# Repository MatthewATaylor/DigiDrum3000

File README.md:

# DigiDrum3000

A real-time FPGA drum sampler, audio effects processor, and audio interface. Visit the [project webpage](https://matthewalantaylor.net/fpga-drums.html) for more information, including a selection of audio demos.

## Branches
- **nexys_a7:** Most recent revision of the project, compatibile with the Nexys A7 FPGA development board (AMD Artix-7). Includes Ethernet audio interface functionality and expression pedal control.
- **urbana:** Original project designed for the Real Digital Urbana FPGA development board (AMD Spartan-7). Developed as the final project for MIT's 6.2050 (Digital Systems Laboratory I). Includes audio visualization functionality.

## Feature Overview (nexys\_a7)
- Drum set audio samples (16-bit, 48 ksps) loaded over UART and stored in DRAM
- MIDI interface for audio sample triggering via an electronic drum set
- Audio effects
  - Pitch shift (resampling)
  - Delay
  - Stereo reverb (Freeverb)
  - Resonant low-pass filter (4-pole transistor ladder filter model)
  - Distortion (tanh)
  - Bit crush
- PCB with patch bay and knobs for controlling effects parameters
- PCB with line-level audio output (TAD5242 DAC) and expression pedal inputs
- UART interface for effects parameter automation in a digital audio workstation
- Audio recording over Ethernet with up to 12 channels of 16-bit samples at 48 ksps.
- 1.5 ms maximum audio latency (from received MIDI message to audio output)
- Extensive testing with cocotb

## Operation
1. Build
```
vivado -mode batch -source build.tcl -tclargs outputDir=<OUTPUT DIRECTORY>
```
2. Program
```
openFPGALoader -b <BOARD_NAME> <OUTPUT DIRECTORY>/final.bit
```
3. Load audio samples
```
python scripts/send_wav.py
```
4. (Optional) Run UART effects parameter controller. Create a new virtual MIDI port if one does not already exist.
```
python scripts/uart_param_controller.py
```
5. (Optional) Run Ethernet audio receiver (requires Linux with PipeWire).
```
cd ethernet_audio_interface
make
./build/ethernet_audio_interface
```

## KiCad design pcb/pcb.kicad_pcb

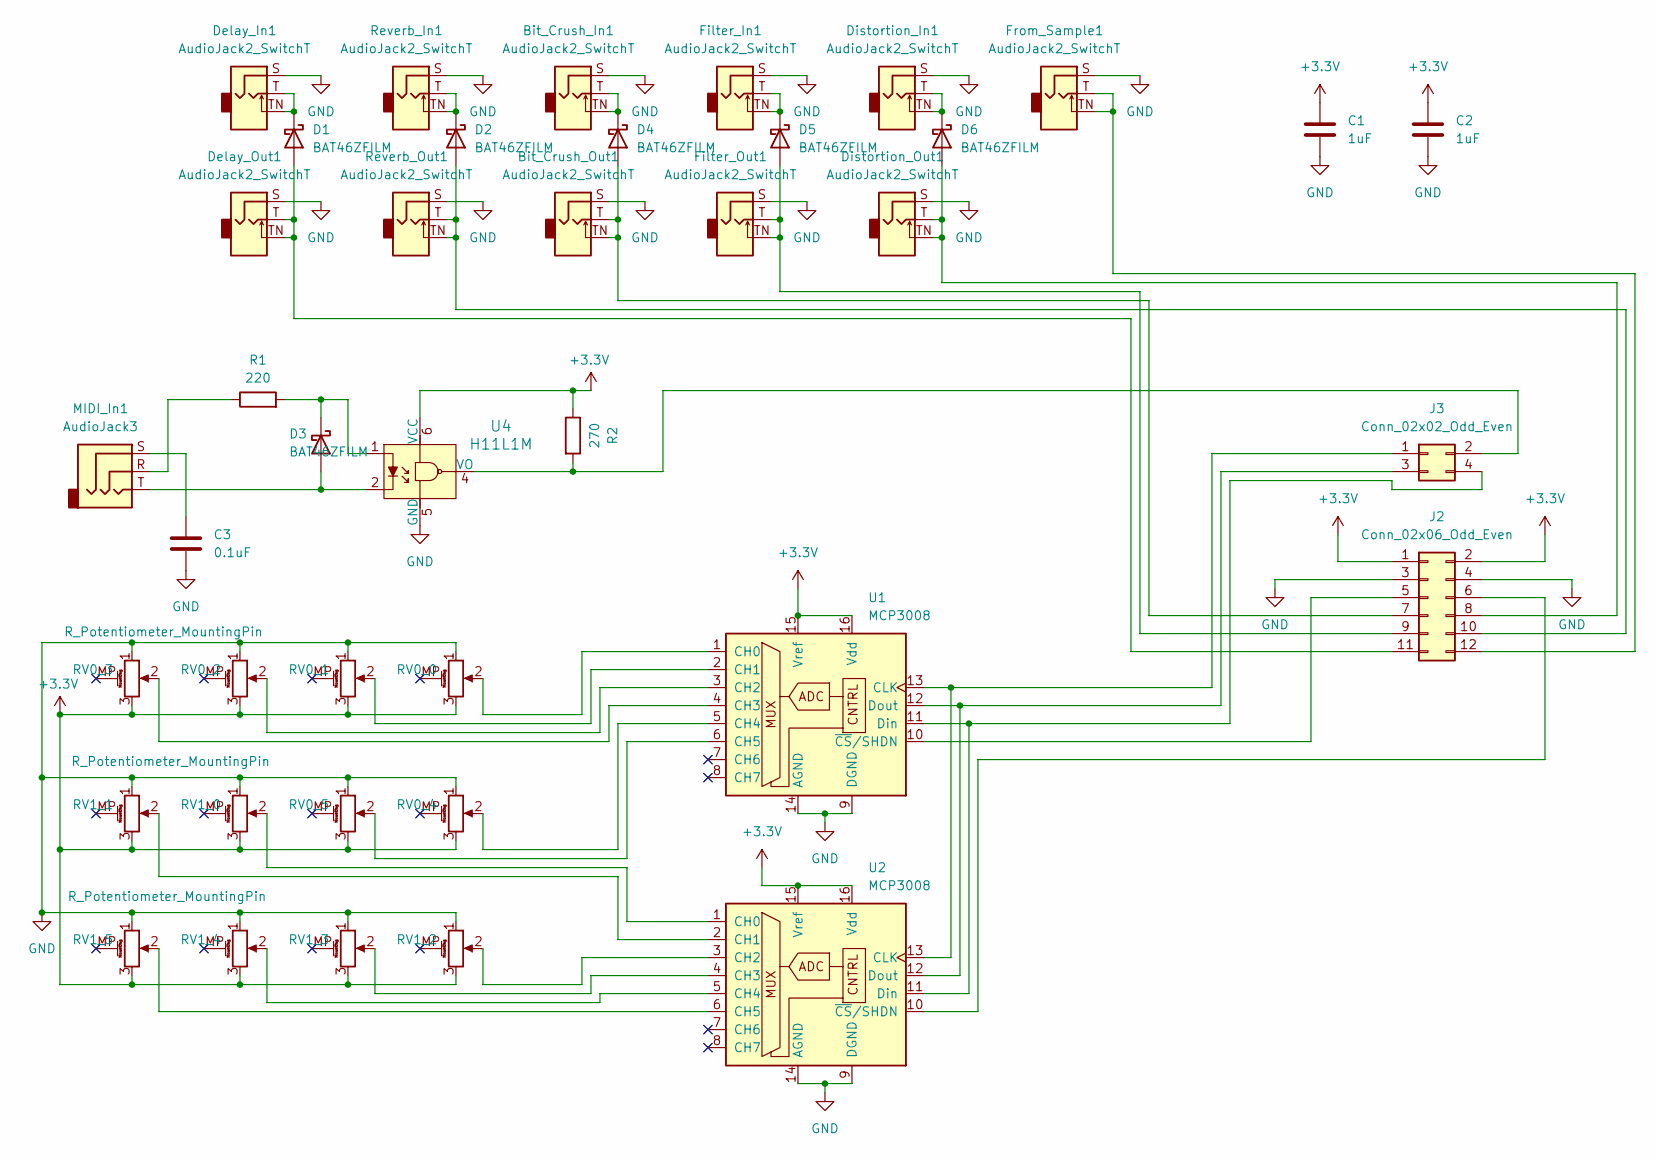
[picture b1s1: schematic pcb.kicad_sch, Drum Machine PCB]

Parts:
Bit_Crush_In1: AudioJack2_SwitchT; Jack_3.5mm_QingPu_WQP-PJ398SM_Vertical_CircularHoles
Bit_Crush_Out1: AudioJack2_SwitchT; Jack_3.5mm_QingPu_WQP-PJ398SM_Vertical_CircularHoles
C1, C2: 1uF; 0805
C3: 0.1uF; 0805
D1, D2, D3, D4, D5, D6: BAT46ZFILM; D_SOD-123
Delay_In1: AudioJack2_SwitchT; Jack_3.5mm_QingPu_WQP-PJ398SM_Vertical_CircularHoles
Delay_Out1: AudioJack2_SwitchT; Jack_3.5mm_QingPu_WQP-PJ398SM_Vertical_CircularHoles
Distortion_In1: AudioJack2_SwitchT; Jack_3.5mm_QingPu_WQP-PJ398SM_Vertical_CircularHoles
Distortion_Out1: AudioJack2_SwitchT; Jack_3.5mm_QingPu_WQP-PJ398SM_Vertical_CircularHoles
Filter_In1: AudioJack2_SwitchT; Jack_3.5mm_QingPu_WQP-PJ398SM_Vertical_CircularHoles
Filter_Out1: AudioJack2_SwitchT; Jack_3.5mm_QingPu_WQP-PJ398SM_Vertical_CircularHoles
From_Sample1: AudioJack2_SwitchT; Jack_3.5mm_QingPu_WQP-PJ398SM_Vertical_CircularHoles
J2: Conn_02x06_Odd_Even; PinHeader_2x06_P2.54mm_Horizontal
J3: Conn_02x02_Odd_Even; PinHeader_2x02_P2.54mm_Horizontal
MIDI_In1: AudioJack3; Jack_3.5mm_QingPu_WQP-PJ366ST_Vertical_CircularHoles
R1: 220; 0805
R2: 270; 0805
RV0_0, RV0_1, RV0_2, RV0_3, RV0_4, RV0_5, RV1_0, RV1_1, RV1_2, RV1_3, RV1_4, RV1_5: R_Potentiometer_MountingPin; Potentiometer_Alpha_RD901F-40-00D_Single_Vertical_MP
Reverb_In1: AudioJack2_SwitchT; Jack_3.5mm_QingPu_WQP-PJ398SM_Vertical_CircularHoles
Reverb_Out1: AudioJack2_SwitchT; Jack_3.5mm_QingPu_WQP-PJ398SM_Vertical_CircularHoles
U1, U2: MCP3008; SOIC-16_W3.90mm
U4: H11L1M; DIP-6_W7.62mm; MPN H11L1M; Digi-Key_PN H11L1-MQT-ND

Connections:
+3.3V: C1.1, C2.1, J2.1, J2.2, R2.1, RV0_0.3, RV0_1.3, RV0_2.3, RV0_3.3, RV0_4.3, RV0_5.3, RV1_0.3, RV1_1.3, RV1_2.3, RV1_3.3, RV1_4.3, RV1_5.3, U1.15 (Vref), U1.16 (Vdd), U2.15 (Vref), U2.16 (Vdd), U4.6 (VCC)
GND: Bit_Crush_In1.S, Bit_Crush_Out1.S, C1.2, C2.2, C3.2, Delay_In1.S, Delay_Out1.S, Distortion_In1.S, Distortion_Out1.S, Filter_In1.S, Filter_Out1.S, From_Sample1.S, J2.3, J2.4, RV0_0.1, RV0_1.1, RV0_2.1, RV0_3.1, RV0_4.1, RV0_5.1, RV1_0.1, RV1_1.1, RV1_2.1, RV1_3.1, RV1_4.1, RV1_5.1, Reverb_In1.S, Reverb_Out1.S, U1.9 (DGND), U1.14 (AGND), U2.9 (DGND), U2.14 (AGND), U4.5 (GND)
unnamed: C3.1, MIDI_In1.S
unnamed: D1.2 (A), Delay_Out1.T, Delay_Out1.TN, J2.11
unnamed: D1.1 (K), Delay_In1.T, Delay_In1.TN
unnamed: D2.2 (A), J2.10, Reverb_Out1.T, Reverb_Out1.TN
unnamed: D2.1 (K), Reverb_In1.T, Reverb_In1.TN
unnamed: D3.2 (A), MIDI_In1.T, U4.2
unnamed: D3.1 (K), R1.2, U4.1
unnamed: Bit_Crush_Out1.T, Bit_Crush_Out1.TN, D4.2 (A), J2.7
unnamed: Bit_Crush_In1.T, Bit_Crush_In1.TN, D4.1 (K)
unnamed: D5.2 (A), Filter_Out1.T, Filter_Out1.TN, J2.9
unnamed: D5.1 (K), Filter_In1.T, Filter_In1.TN
unnamed: D6.2 (A), Distortion_Out1.T, Distortion_Out1.TN, J2.8
unnamed: D6.1 (K), Distortion_In1.T, Distortion_In1.TN
unnamed: J2.5, U1.10 (~CS/SHDN)
unnamed: J2.6, U2.10 (~CS/SHDN)
unnamed: From_Sample1.T, From_Sample1.TN, J2.12
unnamed: J3.1, U1.13 (CLK), U2.13 (CLK)
unnamed: J3.2, R2.2, U4.4 (VO)
unnamed: J3.3, U1.12 (Dout), U2.12 (Dout)
unnamed: J3.4, U1.11 (Din), U2.11 (Din)
unnamed: MIDI_In1.R, R1.1
unnamed: RV0_0.2, U1.1 (CH0)
unnamed: RV0_1.2, U1.2 (CH1)
unnamed: RV0_2.2, U1.3 (CH2)
unnamed: RV0_3.2, U1.4 (CH3)
unnamed: RV0_4.2, U1.5 (CH4)
unnamed: RV0_5.2, U1.6 (CH5)
unnamed: RV1_0.2, U2.1 (CH0)
unnamed: RV1_1.2, U2.2 (CH1)
unnamed: RV1_2.2, U2.3 (CH2)
unnamed: RV1_3.2, U2.4 (CH3)
unnamed: RV1_4.2, U2.5 (CH4)
unnamed: RV1_5.2, U2.6 (CH5)

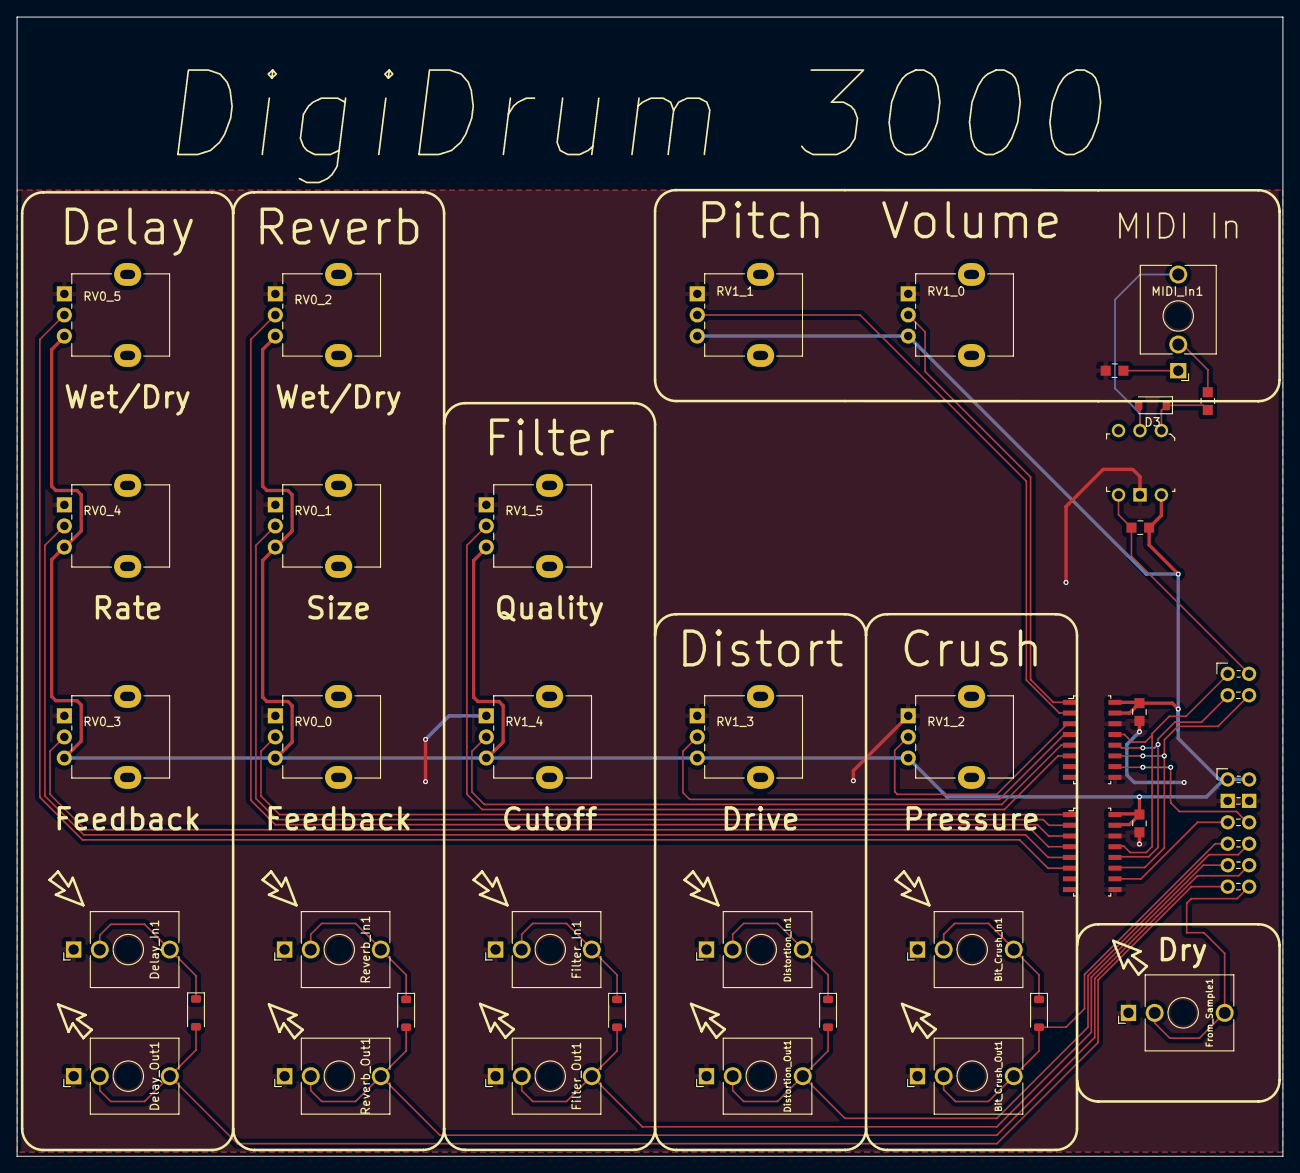
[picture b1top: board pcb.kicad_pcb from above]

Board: 2 copper layers, 150.0 x 135.0 mm, 40 parts (0 on the bottom side), 35 nets.

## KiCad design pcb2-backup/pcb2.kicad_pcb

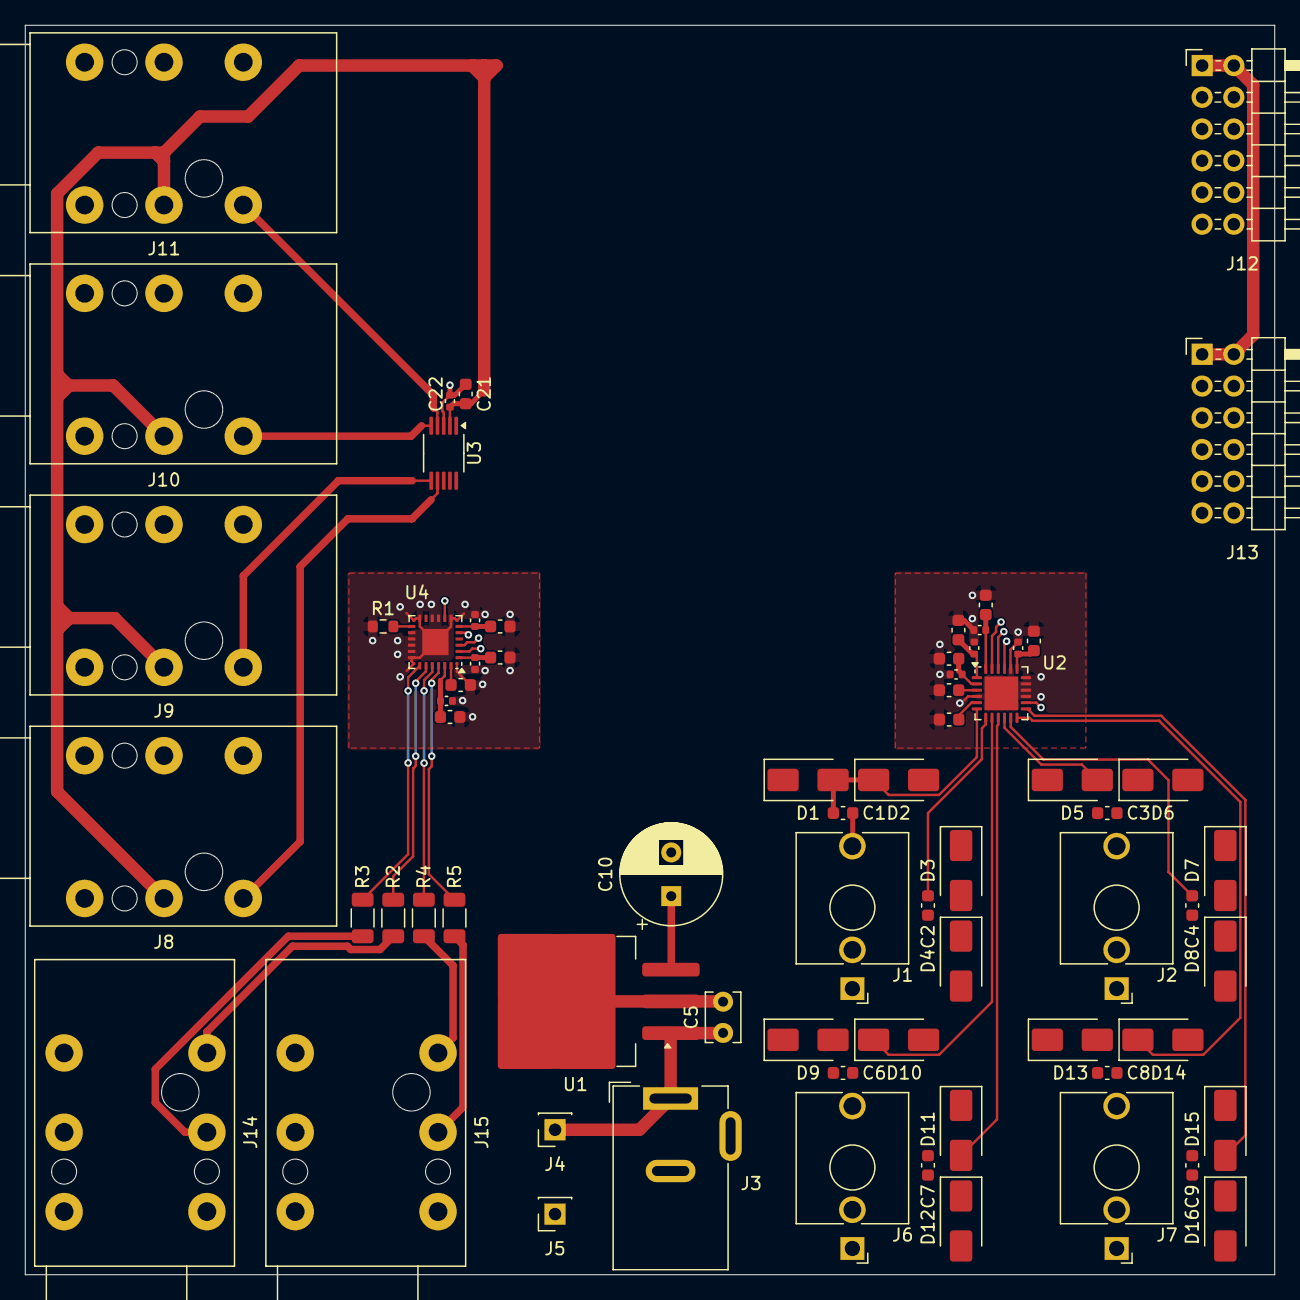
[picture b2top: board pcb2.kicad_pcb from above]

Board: 2 copper layers, 100.0 x 100.0 mm, 69 parts (0 on the bottom side), 50 nets.

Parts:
C1, C2, C3, C4, C6, C7, C8, C9, C14, C17, C19, C23, C26, C28: 10u; C_0603_1608Metric
C5: 4.7u; C_Disc_D3.8mm_W2.6mm_P2.50mm
C10: 100u; CP_Radial_D8.0mm_P3.50mm
C11, C13, C16, C21, C25: 1u; C_0603_1608Metric
C12, C15, C18, C20, C22, C24, C27, C29: 0.1u; C_0402_1005Metric
D1, D2, D3, D4, D5, D6, D7, D8, D9, D10, D11, D12, D13, D14, D15, D16: SS14; D_SMA
J1: WQP419GR_audio_in_1; Jack_3.5mm_QingPu_WQP-PJ366ST_Vertical_CircularHoles
J2: WQP419GR_audio_in_3; Jack_3.5mm_QingPu_WQP-PJ366ST_Vertical_CircularHoles
J3: Barrel_+5V_in; BarrelJack_Wuerth_6941xx301002
J4: Conn_+5V_to_FPGA; PinSocket_1x01_P2.54mm_Vertical
J5: Conn_GND_to_FPGA; PinSocket_1x01_P2.54mm_Vertical
J6: WQP419GR_audio_in_2; Jack_3.5mm_QingPu_WQP-PJ366ST_Vertical_CircularHoles
J7: WQP419GR_audio_in_4; Jack_3.5mm_QingPu_WQP-PJ366ST_Vertical_CircularHoles
J8: ACJS-HHOP_pedal_1; Jack_6.35mm_Neutrik_NRJ6HH_Horizontal
J9: ACJS-HHOP_pedal_2; Jack_6.35mm_Neutrik_NRJ6HH_Horizontal
J10: ACJS-HHOP_pedal_3; Jack_6.35mm_Neutrik_NRJ6HH_Horizontal
J11: ACJS-HHOP_pedal_4; Jack_6.35mm_Neutrik_NRJ6HH_Horizontal
J12: PMOD_JD; PinHeader_2x06_P2.54mm_Horizontal
J13: PMOD_JC; PinHeader_2x06_P2.54mm_Horizontal
J14: ACJS-HHOP_audio_out_L; Jack_6.35mm_Neutrik_NRJ6HH_Horizontal
J15: ACJS-HHOP_audio_out_R; Jack_6.35mm_Neutrik_NRJ6HH_Horizontal
R1: 4.7k; R_0603_1608Metric
R2, R3, R4, R5: 1k; R_1206_3216Metric
U1: LM3940; TO-263-3_TabPin2
U2: PCM1840; Texas_RTW_WQFN-24-1EP_4x4mm_P0.5mm_EP2.7x2.7mm
U3: ADC104S021; VSSOP-10_3x3mm_P0.5mm
U4: TAD5242; Texas_RGE0024C_VQFN-24-1EP_4x4mm_P0.5mm_EP2.1x2.1mm_CornerP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

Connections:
+3.3V: C17.1, C18.1, C21.1, C22.1, C26.1, C27.1, J8.R, J9.R, J10.R, J11.R, J12.1, J12.2, J13.1, J13.2, U2.19 (IOVDD), U3.2 (VA), U4.6 (IOVDD), U4.8 (MD2)
+3.3VA: C10.1, C11.2, C12.2, C23.2, C24.2, D1.1 (K), D3.1 (K), D5.1 (K), D7.1 (K), D9.1 (K), D11.1 (K), D13.1 (K), D15.1 (K), U1.3 (OUT), U2.1 (AVDD), U4.23 (AVDD)
+5V: C5.1, J3.1, J4.1 (Pin_1_1), U1.1 (IN)
/ADC_AUDIO_CLK: J13.8, U2.22 (BCLK)
/ADC_AUDIO_DOUT: J13.10, U2.21 (SDOUT)
/ADC_AUDIO_FSYNC: J13.6, U2.23 (FSYNC)
/ADC_AUDIO_SHDNZ: J13.12, U2.14 (SHDNZ)
/ADC_IN1N: C2.2, D3.2 (A), D4.1 (K), U2.7 (IN1N)
/ADC_IN1P: C1.2, D1.2 (A), D2.1 (K), U2.6 (IN1P)
/ADC_IN2N: C7.2, D11.2 (A), D12.1 (K), U2.9 (IN2N)
/ADC_IN2P: C6.2, D9.2 (A), D10.1 (K), U2.8 (IN2P)
/ADC_IN3N: C4.2, D7.2 (A), D8.1 (K), U2.11 (IN3N)
/ADC_IN3P: C3.2, D5.2 (A), D6.1 (K), U2.10 (IN3P)
/ADC_IN4N: C9.2, D15.2 (A), D16.1 (K), U2.13 (IN4N)
/ADC_IN4P: C8.2, D13.2 (A), D14.1 (K), U2.12 (IN4P)
/ADC_PEDAL_CLK: J13.5, U3.10 (SCLK)
/ADC_PEDAL_CS: J13.11, U3.1 (~CS)
/ADC_PEDAL_DIN: J13.9, U3.8 (DIN)
/ADC_PEDAL_DOUT: J13.7, U3.9 (DOUT)
/DAC_CLK: J12.9, U4.2 (BCLK)
/DAC_DIN: J12.11, U4.5 (DIN)
/DAC_FSYNC: J12.7, U4.3 (FSYNC)
/DAC_OUT1N: R3.2, U4.19 (OUT1N)
/DAC_OUT1P: R2.1, U4.20 (OUT1P)
/DAC_OUT2N: R5.2, U4.22 (OUT2N)
/DAC_OUT2P: R4.1, U4.21 (OUT2P)
GND: C5.2, C10.2, C11.1, C12.1, C13.1, C14.1, C15.1, C16.2, C17.2, C18.2, C19.2, C20.2, C21.2, C22.2, C23.1, C24.1, C25.2, C26.2, C27.2, C28.2, C29.2, D2.2 (A), D4.2 (A), D6.2 (A), D8.2 (A), D10.2 (A), D12.2 (A), D14.2 (A), D16.2 (A), J1.S, J2.S, J3.2, J5.1 (Pin_1_1), J6.S, J7.S, J8.S, J9.S, J10.S, J11.S, J12.3, J12.4, J13.3, J13.4, J14.S, J15.S, R1.1, U1.2 (GND), U2.4 (AVSS), U2.15 (FMT1), U2.16 (FMT0), U2.17 (MSZ), U2.18 (MD0), U2.20 (MD1), U2.25 (PAD), U3.3 (GND), U4.7 (MD1), U4.9 (MD3), U4.10 (MD4), U4.12 (MD5), U4.14 (VSSA), U4.15 (VSSA), U4.16 (VSSA), U4.17 (VSSA), U4.18 (VSSA), U4.25 (PAD), U4.A1 (VSS), U4.A2 (VSS), U4.A3 (VSS), U4.A4 (VSS)
unnamed: C1.1, J1.T
unnamed: C2.1, J1.R
unnamed: C3.1, J2.T
unnamed: C4.1, J2.R
unnamed: C6.1, J6.T
unnamed: C7.1, J6.R
unnamed: C8.1, J7.T
unnamed: C9.1, J7.R
unnamed: J14.R, R3.1
unnamed: J14.T, R2.2
unnamed: J15.R, R5.1
unnamed: J15.T, R4.2
unnamed: C14.2, C15.2, U2.2 (AREG)
unnamed: C19.1, C20.1, U2.24 (DREG)
unnamed: C13.2, U2.5 (MICBIAS)
unnamed: C16.1, U2.3 (VREF)
unnamed: J8.T, U3.7 (IN1)
unnamed: J9.T, U3.6 (IN2)
unnamed: J10.T, U3.5 (IN3)
unnamed: J11.T, U3.4 (IN4)
unnamed: C28.1, C29.1, U4.1 (DREG)
unnamed: R1.2, U4.13 (MD0)
unnamed: C25.1, U4.24 (VREF)

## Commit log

2025-10-06 added gitignore
2025-10-06 updated build.tcl to new version
2025-10-06 added frequency control
2025-10-06 changed frequency bounds
2025-10-07 designed CORDIC sin routine in python
2025-10-07 implimented CORDID sin calculation
2025-10-07 updated gitignore
2025-10-07 reduced cost of CORDIC module
2025-10-07 added [untested] basic delta sigma dac
2025-10-07 added divider
2025-10-08 completed sin support
2025-10-08 expanded sin generator testing
2025-10-08 added testbench for delta-sigma dac, trying to debug 2nd order harmonic in sin_gen -> dlt_sig_dac_1st_order -> audio output on FPGA board
2025-10-08 expanded test coverage
2025-10-09 made combined testbench and confirmed that observed harmonic distortion has to do with analog part
2025-10-09 actually used correct build.tcl file
2025-10-10 changed DAC to drive between 0 and 0.5Vdd instead of 0 to Vdd, eliminated harmonic distortion (at least what's visible on occiliscope with -50dB noise floor)
2025-10-10 measured response of analog filter on FPGA
2025-10-10 upgraded dac frequency response sim
2025-10-10 implimented 2nd order delta sigma DAC with -91 dB overall THDN and -97dB THDN in audable range
2025-10-11 important note added: USE 2264 CYCLES PER SAMPLE
2025-10-11 designed minimum phase 1024 width lowpass filter for DAC upsampling
2025-10-13 updated filter stuff
2025-10-14 changed filter for 16x oversampling
2025-10-15 once again updated filter design
2025-10-15 first dac filter implimentation attempt, changing back filter encoding to make sense
2025-10-21 tested upsampler, has odd (assumed clipping related) bug at large values
2025-10-22 changed upsampler to use distributed ram instead of a second BRAM18 block
2025-10-22 started working on the pcb design
2025-10-23 completed circuit design
2025-10-23 removed backup files from git tracking
2025-10-23 added footprints to pcb and updated gitignore to include kicad.gitignore
2025-10-24 layed out pcb and adjusted design to meet Spartan 7 GPIO spec
2025-10-24 finished pretty-ing up pcb layout
2025-10-24 updated pcb based on schottky diodes availible from lab on floor 5
2025-10-25 updated delta-sigma sim
2025-10-25 got testbench to match what I'm hearing in terms of noise
2025-10-25 delta-sigma modulator sounds better without dither for some reason - need to look into dither technique
2025-10-29 confirmed lack of need for dithering in delta sigma dac
2025-10-29 Add gitignore
2025-10-29 rm _history
2025-10-30 finish test_midi_processor
2025-10-30 Add video clocks, remove IBUFs before MMCMs to ease clk routing (IBUFs probably unnecessary but we should verify)
2025-10-30 change dram_writer clk domain to clk_pixel, plus other alignments with block diagram
2025-10-31 Add video support to dram controller interface. traffic_generator read_data_video FIFO tlast coming a bit too late.
2025-10-31 Fix video offset issue: properly initialize video logic and synchronize with DRAM output
2025-10-31 finally implimented dither correctly
2025-10-31 initial implimentation of note_tracker and video_sig_gen_basic
2025-10-31 fixed silly typos
2025-11-02 add a hacky combinational pitch (potentiometer) to sample rate converter
2025-11-02 removed old test code
2025-11-03 completed basic video response
2025-11-03 switched dry_gen to use direct sample peak rather than midi trigger
2025-11-05 added snare/hihat shapes, made bass drum shape not use DSP blocks
2025-11-07 changed dry_gen so individual shapes can apply instrument intensity according to their own rules
2025-11-07 added animated testbench for quicker prototyping
2025-11-07 Add Farrow resampler. Occasional glitches - need to rearrange operations.
2025-11-07 updated note tracking to somewhat deprioritized very low frequencies (<60Hz)
2025-11-07 Track changes in sample_period for smoother resampling
2025-11-07 Clean up resampler and tests
2025-11-08 Update Farrow resampler to do upsampling only (uses 7 DSP blocks now)
2025-11-08 Renaming
2025-11-09 added and tested patch reconstructor
2025-11-09 fixed my mistake THAT I COULD HAVE CAUGHT WITH DRC that seperates a trace from the pins by .1mm
2025-11-09 integrated patch detection into actual use
2025-11-09 made dry_pin pullup instead of true 1 to avoid shorts with ground when plugging in patch cables
2025-11-09 finished pcb interface
2025-11-11 Finish functional but un-implementable downsampler (now need to handle buffer memory usage)
2025-11-11 Finish resampler
2025-11-11 Remove old downsampler
2025-11-12 added a bunch of stuff to dry_gen
2025-11-12 pitch_to_sample_period takes 3 clock cycles now
2025-11-14 added basic delay functionality
2025-11-15 Add some tests for tracking down audio crackle
2025-11-15 Start resizing FIFOs
2025-11-15 Test sound of sample_period being held for 8 samples
2025-11-15 Fix crackling audio (store sample_period in memory command_fifo)
2025-11-15 Remove sample period hold logic
2025-11-15 Clean up tests
2025-11-16 Add very simple audio delay - uses 30 RAMB36
2025-11-16 Fix some bit width warnings
2025-11-16 Add delay feedback and change controls for testing without PCB
2025-11-16 polished delay_gen main module and changed note_tracker back to midi
2025-11-16 adjusted delay_gen timing to match audio_delay
2025-11-17 created test bench for delay shapes
2025-11-17 added circle to delay shapes
2025-11-18 added star and cross delay shapes
2025-11-18 finished delay shapes
2025-11-18 added color gradient
2025-11-18 added small dither to remove banding in gradient
2025-11-19 Switch to resampling audio delay
2025-11-19 Improve Farrow timing
2025-11-20 Move downsampler sample buffer to BRAM
2025-11-21 Add fast/slow delay switch
2025-11-21 Remove a file that I think REAPER decided to create
2025-11-21 added bit crushing to video side
2025-11-21 Add controls for rest of audio delay parameters
2025-11-21 Add audio crush
2025-11-21 Fix MIDI channel
2025-11-22 added video_distortion and adjusted video_crush
2025-11-22 adjusted delay_gen
2025-11-22 added volume control and a few adjustments
2025-11-23 Play with integrators
2025-11-25 Add Python and SV ladder filters, but the SV one is very unrealistic right now
2025-11-25 Fix timing issues (upsampler, audio_filter)
2025-11-25 Forgot to reset a register
2025-11-25 initial video filter implimentation
2025-11-26 Clean up audio_filter and match to the Python implementation
2025-11-28 Implement floating point Freeverb in Python
2025-11-28 Remove REAPER file
2025-11-29 Implement fixed point Freeverb
2025-12-01 Add audio_reverb. Simulated and built, but not yet hardware-tested
2025-12-01 Add registers to resampler and reduce DSP slice usage, confirm functioning hardware
2025-12-02 added exponential calculator for use in video filter
2025-12-02 finished basic video filter
2025-12-02 Add tanh approximation
2025-12-02 Remove unused CORDIC files
2025-12-03 Generalize the upsampler to use for audio effects oversampling
2025-12-03 Add audio_distortion
2025-12-03 Increase distortion gain
2025-12-03 Seems like adding registers at the audio outputs helps with noise a little?
2025-12-03 Move audio blocks to audio_processor, add audio_multi_mux
2025-12-03 fixed gaussian coefficients to actually be gaussian
2025-12-04 added and tested YCoCg_422 encoding
2025-12-05 Rewrite audio_filter to use way fewer resources, support oversampling, and have tanh feedback
2025-12-05 created video reverb skeleton
2025-12-05 changed stacker to auto-align tlast signal
2025-12-05 Add velocity sensitivity, remove upsampler latch
2025-12-05 Was too stingy with filter optimization. Bringing back some bits.
2025-12-06 finished initial video_reverb implimentation
2025-12-06 fixed display flickering/cutting out when changing patch
2025-12-06 first attempt at all samples together
2025-12-06 Fix audio sample writer
2025-12-06 fixed visuals for full instruments
2025-12-07 Add UART parameter automation
2025-12-07 A tiny bit of clean up
2025-12-10 Add some additional code for simulation and plot generation
2026-01-08 Add Nexys 4 DDR compatible branch (audio only)
2026-01-08 Add README.md
2026-01-30 Add initial Ethernet TX
2026-02-19 Add PCB interface
2026-03-18 Change velocity curve to piecewise linear
2026-03-18 Fix tanh sim
2026-04-09 Add compressed audio samples, create KiCad project for new PCB
2026-04-10 Fix sample mixer
2026-06-07 Implement expression pedal controls
2026-06-07 Begin testing eth_transmit again
2026-06-09 Complete eth_transmit module
2026-06-10 Add Ethernet audio interface driver
2026-06-11 Add dac_controller for TAD5242
2026-06-11 Change most logic (except audio effects) to use 48 kHz sample rate. Getting error that xpm_fifo_axis not found...
2026-06-11 More build attempts
2026-06-12 Fix build issues. Now need to fix timing.
2026-06-13 Incorporate recording for all instruments and fix timing issues
2026-06-13 Remove unwanted KiCad files
2026-06-13 Remove README.md
2026-06-14 Create LICENSE
2026-06-15 Update filter coefficients
2026-06-16 Ethernet driver debugging
2026-06-16 Implement adaptive resampling on FPGA and corresponding (not-yet-tuned) driver code
2026-06-17 Optimize recording interface for low latency and no xruns
2026-06-17 Measure Ethernet roundtrip latency
2026-06-19 Add external audio input support
2026-06-20 Use BRAM for Ethernet audio buffer
2026-06-21 Add project webpage link to README.md
